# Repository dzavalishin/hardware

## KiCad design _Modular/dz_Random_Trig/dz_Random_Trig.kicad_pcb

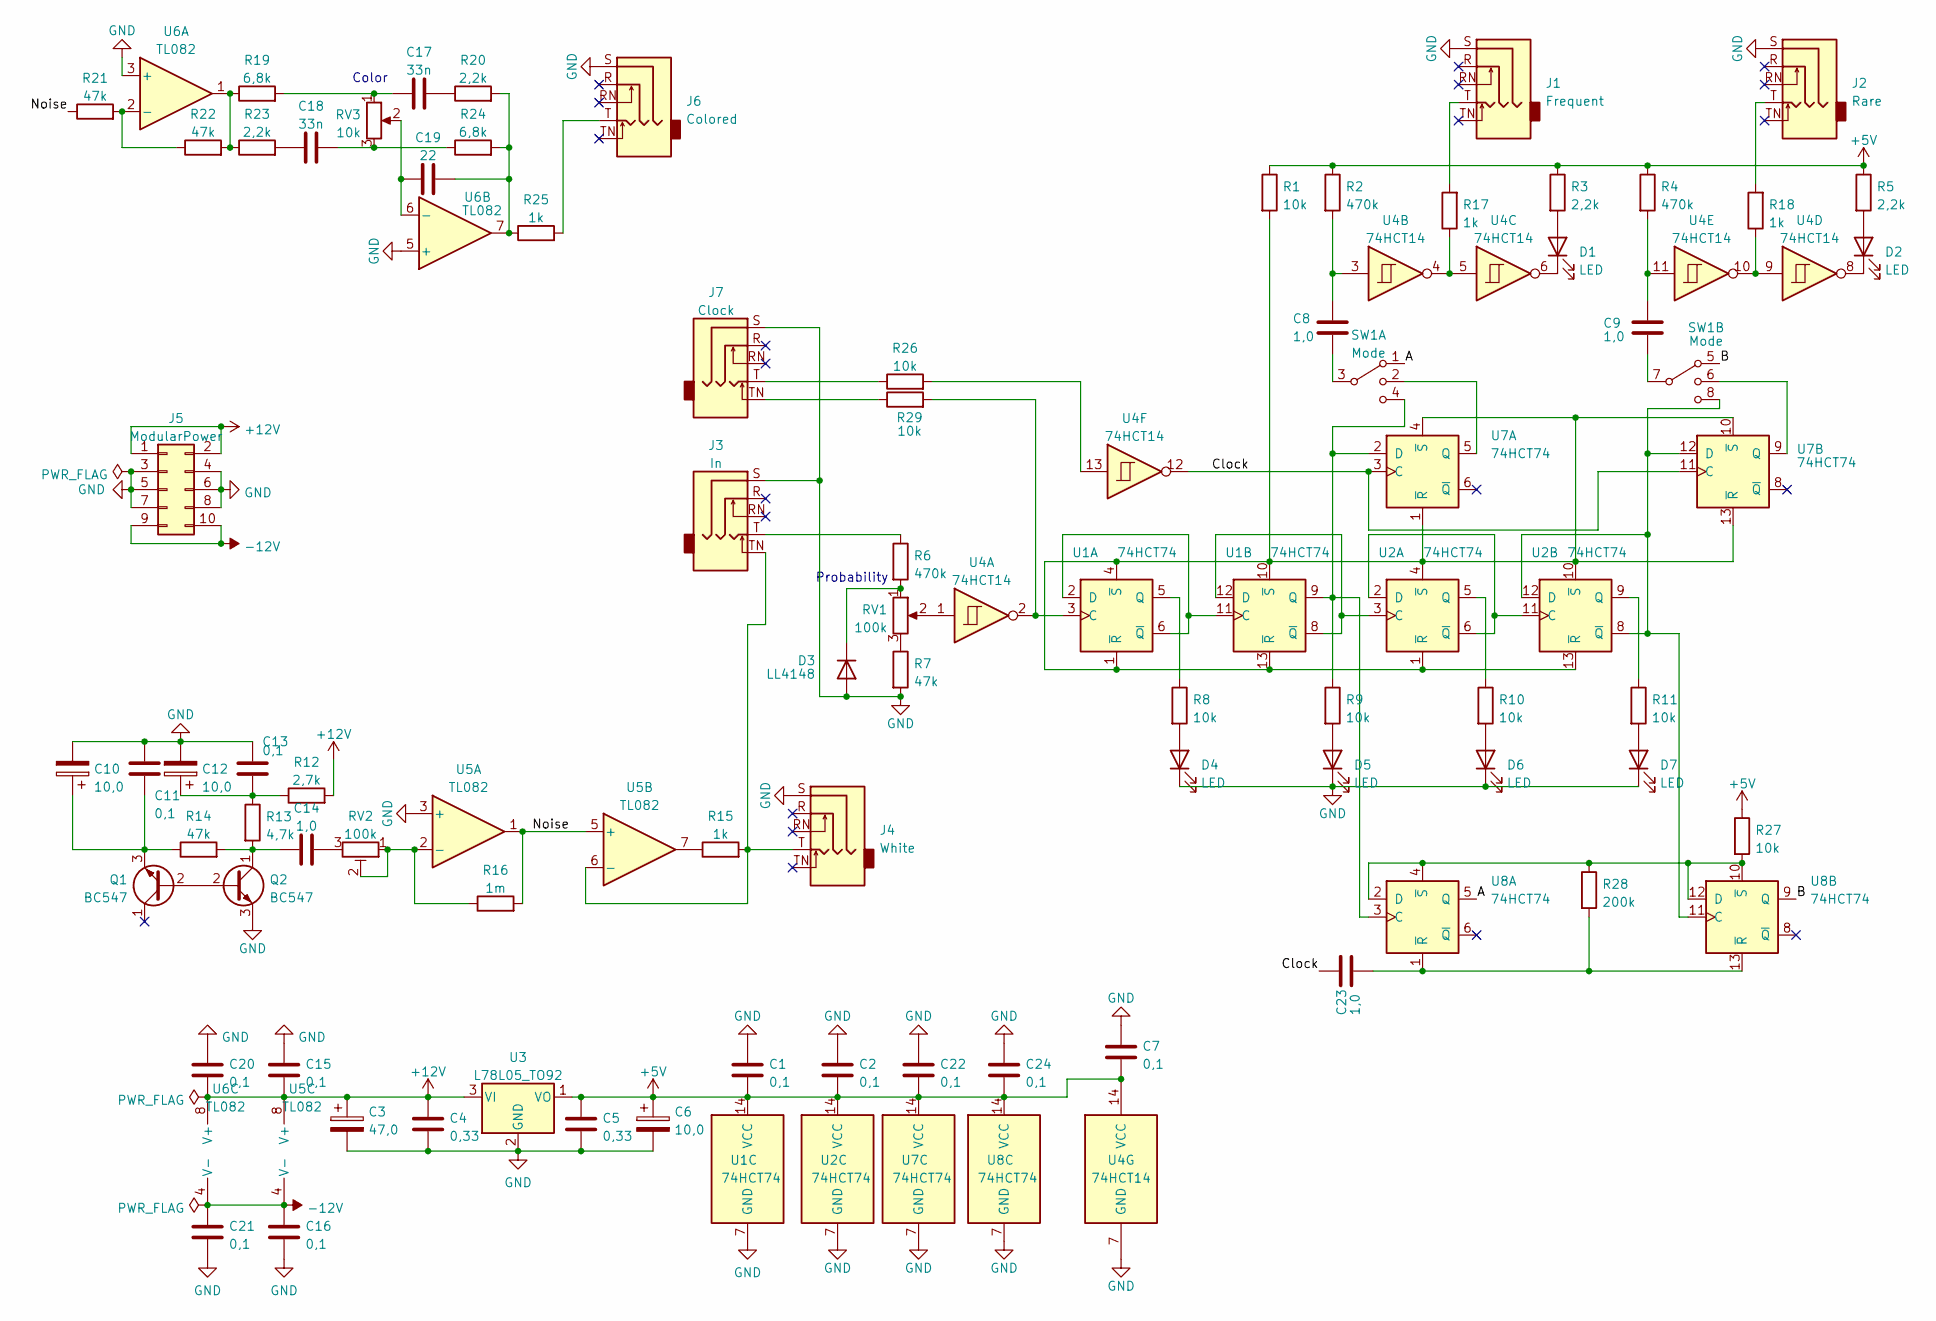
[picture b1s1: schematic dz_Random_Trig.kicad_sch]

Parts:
C1, C2, C7, C11, C13, C15, C16, C20, C21, C22, C24: 0,1; C_0805_2012Metric_Pad1.18x1.45mm_HandSolder
C3: 47,0; CP_Elec_6.3x5.2
C4, C5: 0,33; C_0805_2012Metric_Pad1.18x1.45mm_HandSolder
C6, C10, C12: 10,0; CP_Elec_4x5.4
C8, C9, C14, C23: 1,0; C_0805_2012Metric_Pad1.18x1.45mm_HandSolder
C17, C18: 33n; C_0805_2012Metric_Pad1.18x1.45mm_HandSolder
C19: 22; C_0805_2012Metric_Pad1.18x1.45mm_HandSolder
D1, D2, D4, D5, D6, D7: LED; LED_D3.0mm
D3: LL4148; D_MiniMELF
J1: Frequent; Jack_3.5mm_CUI_SJ1-3525N_Horizontal
J2: Rare; Jack_3.5mm_CUI_SJ1-3525N_Horizontal
J3: In; Jack_3.5mm_CUI_SJ1-3525N_Horizontal
J4: White; Jack_3.5mm_CUI_SJ1-3525N_Horizontal
J5: ModularPower; PinHeader_2x05_P2.54mm_Vertical
J6: Colored; Jack_3.5mm_CUI_SJ1-3525N_Horizontal
J7: Clock; Jack_3.5mm_CUI_SJ1-3525N_Horizontal
Q1, Q2: BC547; TO-92_Inline
R1, R8, R9, R10, R11, R26, R27, R29: 10k; R_0805_2012Metric_Pad1.20x1.40mm_HandSolder
R2, R4, R6: 470k; R_0805_2012Metric_Pad1.20x1.40mm_HandSolder
R3, R5, R20, R23: 2,2k; R_0805_2012Metric_Pad1.20x1.40mm_HandSolder
R7, R14, R21, R22: 47k; R_0805_2012Metric_Pad1.20x1.40mm_HandSolder
R12: 2,7k; R_0805_2012Metric_Pad1.20x1.40mm_HandSolder
R13: 4,7k; R_0805_2012Metric_Pad1.20x1.40mm_HandSolder
R15, R17, R18, R25: 1k; R_0805_2012Metric_Pad1.20x1.40mm_HandSolder
R16: 1m; R_0805_2012Metric_Pad1.20x1.40mm_HandSolder
R19, R24: 6,8k; R_0805_2012Metric_Pad1.20x1.40mm_HandSolder
R28: 200k; R_0805_2012Metric_Pad1.20x1.40mm_HandSolder
RV1: 100k; Potentiometer_Alps_RK097_Single_Horizontal
RV2: 100k; Potentiometer_Runtron_RM-065_Vertical
RV3: 10k; Potentiometer_Alps_RK097_Single_Horizontal
SW1: Mode
U1, U2, U7, U8: 74HCT74; DIP-14_W7.62mm_Socket_LongPads
U3: L78L05_TO92; TO-92_Inline
U4: 74HCT14; DIP-14_W7.62mm_Socket_LongPads
U5, U6: TL082; DIP-8_W7.62mm_Socket_LongPads

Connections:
+5V: C1.2, C2.2, C5.1, C6.1, C7.2, C22.2, C24.2, R1.1, R2.1, R3.1, R4.1, R5.1, R27.1, U1.14 (VCC), U2.14 (VCC), U3.1 (VO), U4.14 (VCC), U7.14 (VCC), U8.14 (VCC)
+12V: C3.1, C4.1, C15.2, C20.2, J5.1, J5.2, R12.2, U3.3 (VI), U5.8 (V+), U6.8 (V+)
-12V: C16.1, C21.1, J5.9, J5.10, U5.4 (V-), U6.4 (V-)
GND: C1.1, C2.1, C3.2, C4.2, C5.2, C6.2, C7.1, C10.2, C11.1, C12.2, C13.1, C15.1, C16.2, C20.1, C21.2, C22.1, C24.1, D3.2 (A), D4.1 (K), D5.1 (K), D6.1 (K), D7.1 (K), J1.S, J2.S, J3.S, J4.S, J5.3, J5.4, J5.5, J5.6, J5.7, J5.8, J6.S, J7.S, Q2.3 (E), R7.2, U1.7 (GND), U2.7 (GND), U3.2 (GND), U4.7 (GND), U5.3 (+), U6.3 (+), U6.5 (+), U7.7 (GND), U8.7 (GND)
unnamed: C8.2, SW1.2, SW1.3, U7.5 (Q)
unnamed: C9.2, SW1.6, SW1.7, U7.9 (Q)
unnamed: C10.1, C11.2, Q1.3 (E), R14.1
unnamed: C12.1, C13.2, R12.1, R13.1
unnamed: C14.1, Q2.1 (C), R13.2, R14.2
unnamed: C14.2, RV2.3
unnamed: C17.1, R19.2, RV3.1
unnamed: C17.2, R20.1
unnamed: C18.1, R23.2
unnamed: C18.2, R24.1, RV3.3
unnamed: C19.1, RV3.2, U6.6 (-)
unnamed: C19.2, R20.2, R24.2, R25.1, U6.7
unnamed: C23.2, R28.2, U8.1 (~R), U8.13 (~R)
unnamed: D1.1 (K), U4.6
unnamed: D1.2 (A), R3.2
unnamed: D2.1 (K), U4.8
unnamed: D2.2 (A), R5.2
unnamed: D3.1 (K), R6.2, RV1.1
unnamed: D4.2 (A), R8.2
unnamed: D5.2 (A), R9.2
unnamed: D6.2 (A), R10.2
unnamed: D7.2 (A), R11.2
unnamed: J1.T, R17.2
unnamed: J2.T, R18.2
unnamed: J3.T, R6.1
unnamed: J6.T, R25.2
unnamed: J7.T, R26.1
unnamed: Q1.2 (B), Q2.2 (B)
unnamed: R7.1, RV1.3
unnamed: R15.1, U5.7
unnamed: R16.1, RV2.1, RV2.2, U5.2 (-)
unnamed: R19.1, R22.2, R23.1, U6.1
unnamed: R21.2, R22.1, U6.2 (-)
unnamed: R26.2, U4.13
unnamed: R27.2, R28.1, U8.2 (D), U8.4 (~S), U8.10 (~S), U8.12 (D)
unnamed: SW1.1, U8.5 (Q)
unnamed: SW1.5, U8.9 (Q)
unnamed: U1.2 (D), U1.6 (~Q), U1.11 (C)
unnamed: R8.1, U1.5 (Q)
unnamed: U1.8 (~Q), U1.12 (D), U2.3 (C)
unnamed: R9.1, SW1.4, U1.9 (Q), U7.2 (D), U8.3 (C)
unnamed: R1.2, U1.1 (~R), U1.4 (~S), U1.10 (~S), U1.13 (~R), U2.1 (~R), U2.4 (~S), U2.10 (~S), U2.13 (~R), U7.1 (~R), U7.4 (~S), U7.10 (~S), U7.13 (~R)
unnamed: R10.1, U2.5 (Q)
unnamed: U2.2 (D), U2.6 (~Q), U2.11 (C)
unnamed: R11.1, U2.9 (Q)
unnamed: SW1.8, U2.8 (~Q), U2.12 (D), U7.12 (D), U8.11 (C)
unnamed: RV1.2, U4.1
unnamed: C8.1, R2.2, U4.3
unnamed: R17.1, U4.4, U4.5
unnamed: R18.1, U4.9, U4.10
unnamed: C9.1, R4.2, U4.11
unnamed: C23.1, U4.12, U7.3 (C), U7.11 (C)

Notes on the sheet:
Probability
Color

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
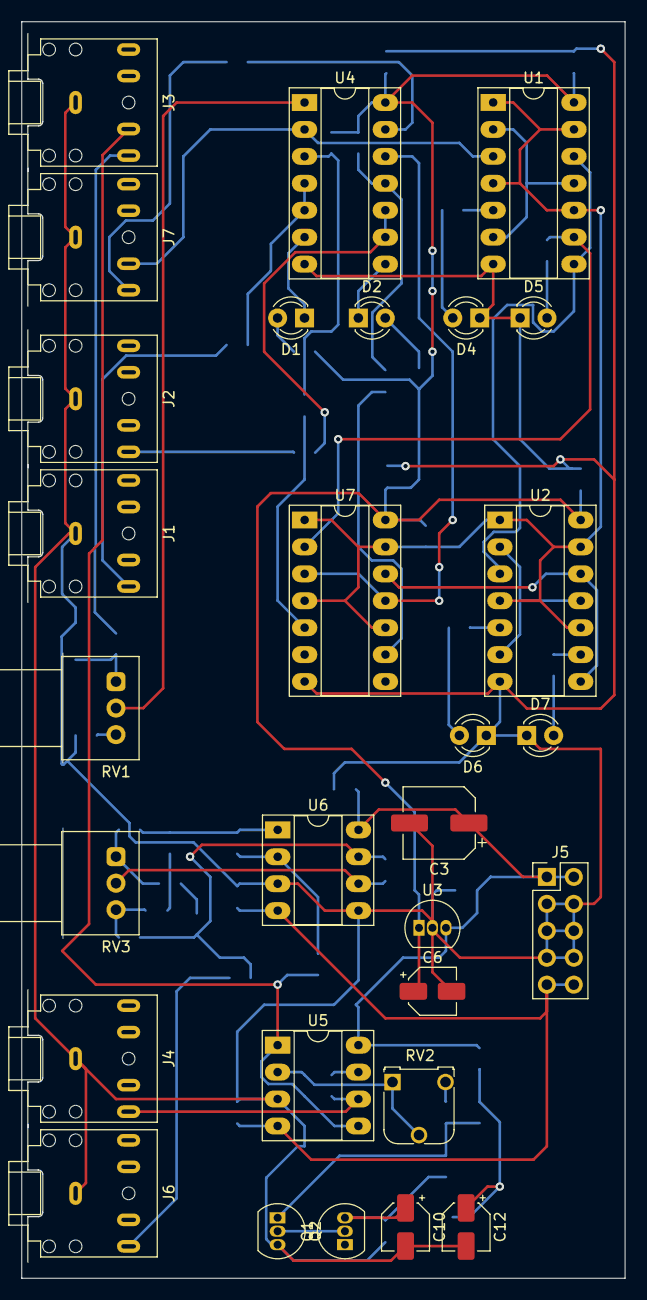
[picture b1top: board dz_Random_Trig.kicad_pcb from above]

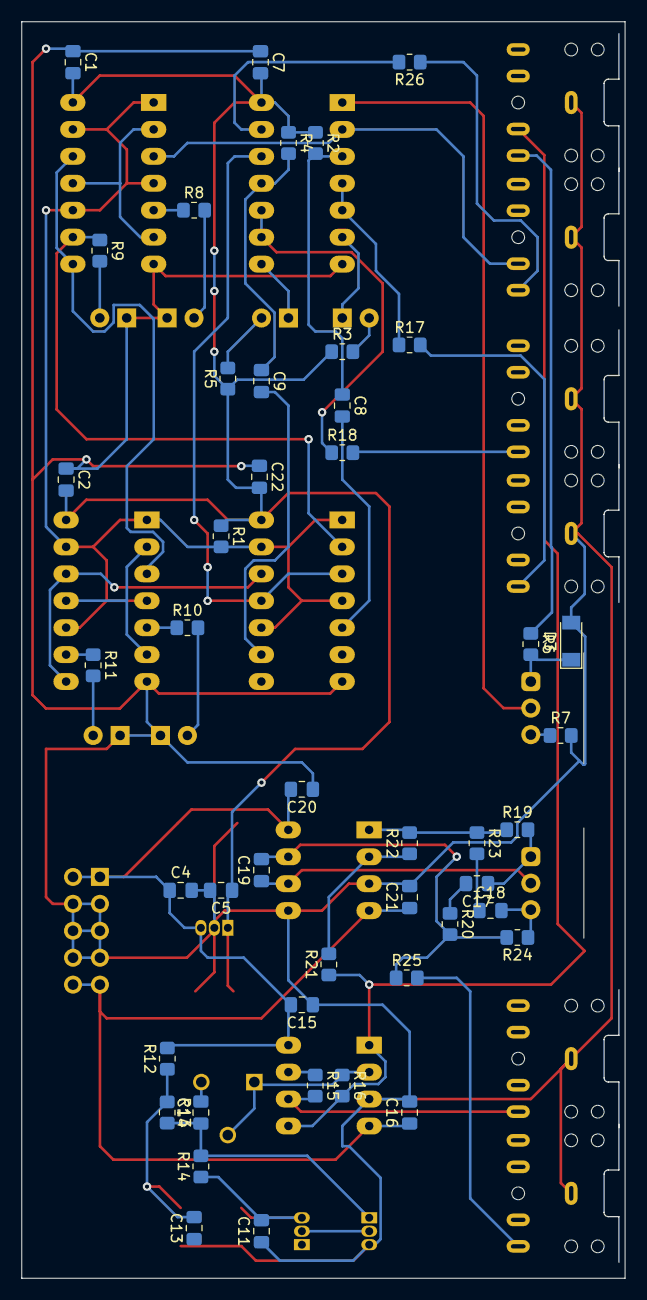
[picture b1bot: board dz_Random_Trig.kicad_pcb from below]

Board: 2 copper layers, 56.9 x 118.5 mm, 74 parts (45 on the bottom side), 55 nets.

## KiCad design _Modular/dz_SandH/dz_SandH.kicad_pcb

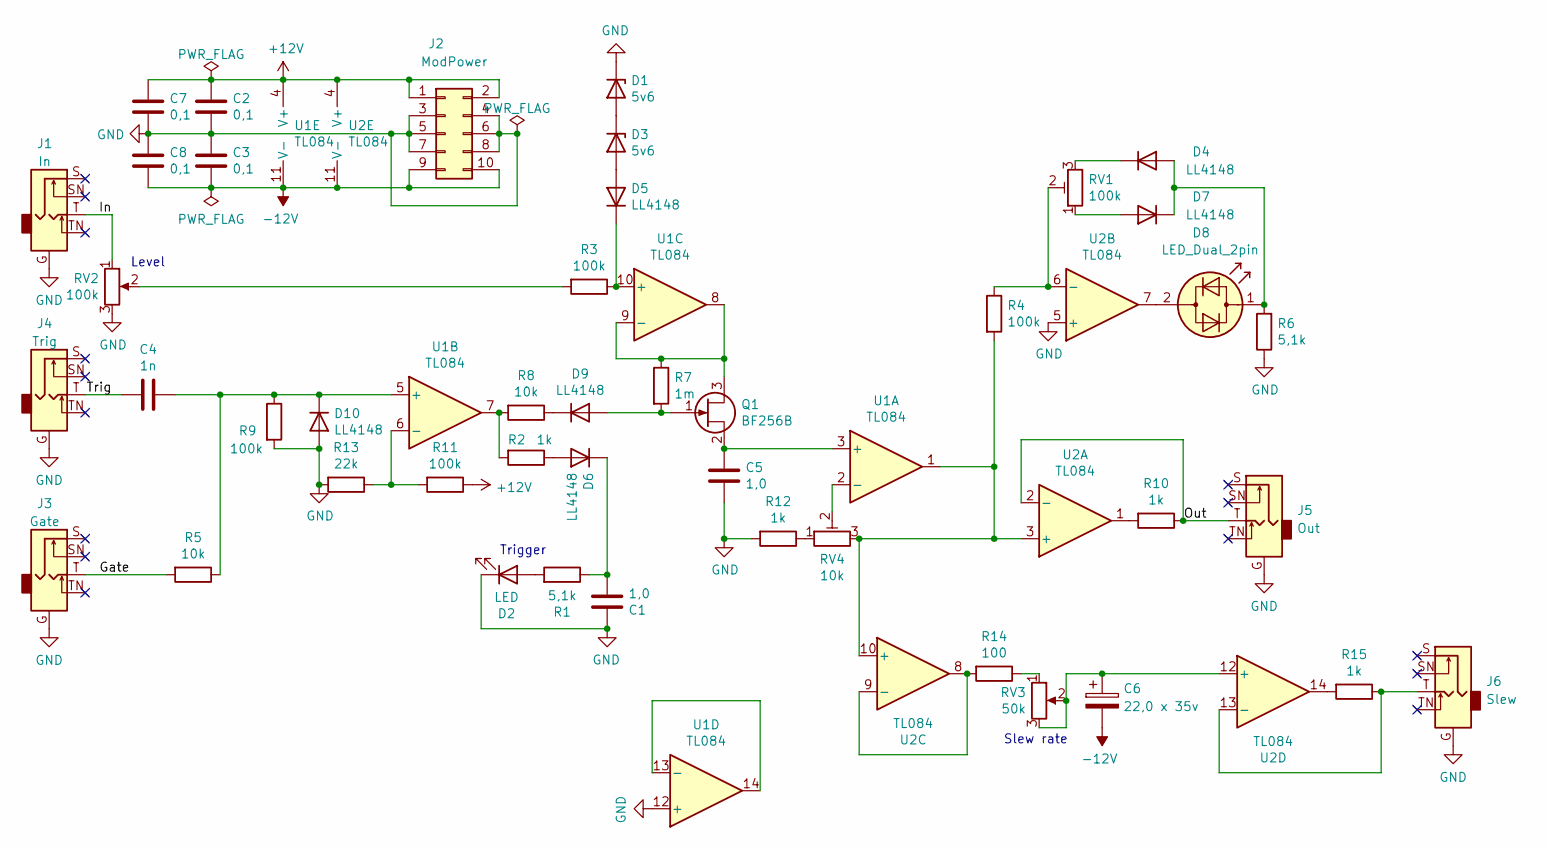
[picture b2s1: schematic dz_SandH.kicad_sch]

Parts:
C1, C5: 1,0; C_0805_2012Metric_Pad1.18x1.45mm_HandSolder
C2, C3, C7, C8: 0,1; C_0805_2012Metric_Pad1.18x1.45mm_HandSolder
C4: 1n; C_0805_2012Metric_Pad1.18x1.45mm_HandSolder
C6: 22,0 x 35v; CP_Radial_D8.0mm_P2.50mm
D1, D3: 5v6; D_MiniMELF_Handsoldering
D2: LED; LED_D3.0mm_Horizontal_O1.27mm_Z2.0mm
D4, D5, D6, D7, D9, D10: LL4148; D_MiniMELF
D8: LED_Dual_2pin; LED_D3.0mm_Horizontal_O1.27mm_Z2.0mm
J1: In; Jack_3.5mm_CUI_SJ1-3525N_Horizontal
J2: ModPower; PinHeader_2x05_P2.54mm_Vertical
J3: Gate; Jack_3.5mm_CUI_SJ1-3525N_Horizontal
J4: Trig; Jack_3.5mm_CUI_SJ1-3525N_Horizontal
J5: Out; Jack_3.5mm_CUI_SJ1-3525N_Horizontal
J6: Slew; Jack_3.5mm_CUI_SJ1-3525N_Horizontal
Q1: BF256B; TO-92
R1, R6: 5,1k; R_0805_2012Metric_Pad1.20x1.40mm_HandSolder
R2, R10, R12, R15: 1k; R_0805_2012Metric_Pad1.20x1.40mm_HandSolder
R3, R4, R9, R11: 100k; R_0805_2012Metric_Pad1.20x1.40mm_HandSolder
R5, R8: 10k; R_0805_2012Metric_Pad1.20x1.40mm_HandSolder
R7: 1m; R_0805_2012Metric_Pad1.20x1.40mm_HandSolder
R13: 22k; R_0805_2012Metric_Pad1.20x1.40mm_HandSolder
R14: 100; R_0805_2012Metric_Pad1.20x1.40mm_HandSolder
RV1: 100k; Potentiometer_Runtron_RM-065_Vertical
RV2: 100k; Potentiometer_Alps_RK097_Single_Horizontal
RV3: 50k; Potentiometer_Alps_RK097_Single_Horizontal
RV4: 10k; Potentiometer_Runtron_RM-065_Vertical
U1, U2: TL084; DIP-14_W7.62mm_Socket_LongPads

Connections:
+12V: C2.1, C7.1, J2.1, J2.2, R11.1, U1.4 (V+), U2.4 (V+)
-12V: C3.2, C6.2, C8.2, J2.9, J2.10, U1.11 (V-), U2.11 (V-)
/Gate: J3.T, R5.2
/In: J1.T, RV2.1
/Out: J5.T, R10.1, U2.2 (-)
/Trig: C4.2, J4.T
GND: C1.1, C2.2, C3.1, C5.2, C7.2, C8.1, D1.1 (K), D2.1 (K), D10.2 (A), J1.G, J2.3, J2.4, J2.5, J2.6, J2.7, J2.8, J3.G, J4.G, J5.G, J6.G, R6.1, R9.2, R12.2, R13.2, RV2.3, U1.12 (+), U2.5 (+)
unnamed: C1.2, D6.1 (K), R1.1
unnamed: C5.1, Q1.2 (S), U1.3 (+)
unnamed: C6.1, RV3.2, RV3.3, U2.12 (+)
unnamed: D1.2 (A), D3.1 (K)
unnamed: D3.2 (A), D5.2 (A)
unnamed: D4.1 (K), RV1.3
unnamed: D4.2 (A), D7.1 (K), D8.1 (KA), R6.2
unnamed: D5.1 (K), R3.1, U1.10 (+)
unnamed: D6.2 (A), R2.1
unnamed: D7.2 (A), RV1.1
unnamed: D8.2 (AK), U2.7
unnamed: C4.1, D10.1 (K), R5.1, R9.1, U1.5 (+)
unnamed: J6.T, R15.1, U2.13 (-)
unnamed: D9.2 (A), Q1.1 (G), R7.2
unnamed: Q1.3 (D), R7.1, U1.8, U1.9 (-)
unnamed: D2.2 (A), R1.2
unnamed: R4.2, RV4.3, U1.1, U2.3 (+), U2.10 (+)
unnamed: D9.1 (K), R8.1
unnamed: R2.2, R8.2, U1.7
unnamed: R10.2, U2.1
unnamed: R11.2, R13.1, U1.6 (-)
unnamed: R12.1, RV4.1
unnamed: R14.1, RV3.1
unnamed: R14.2, U2.8, U2.9 (-)
unnamed: R15.2, U2.14
unnamed: R4.1, RV1.2, U2.6 (-)
unnamed: R3.2, RV2.2
unnamed: RV4.2, U1.2 (-)
unnamed: U1.13 (-), U1.14

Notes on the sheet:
Trigger
Slew rate
Level

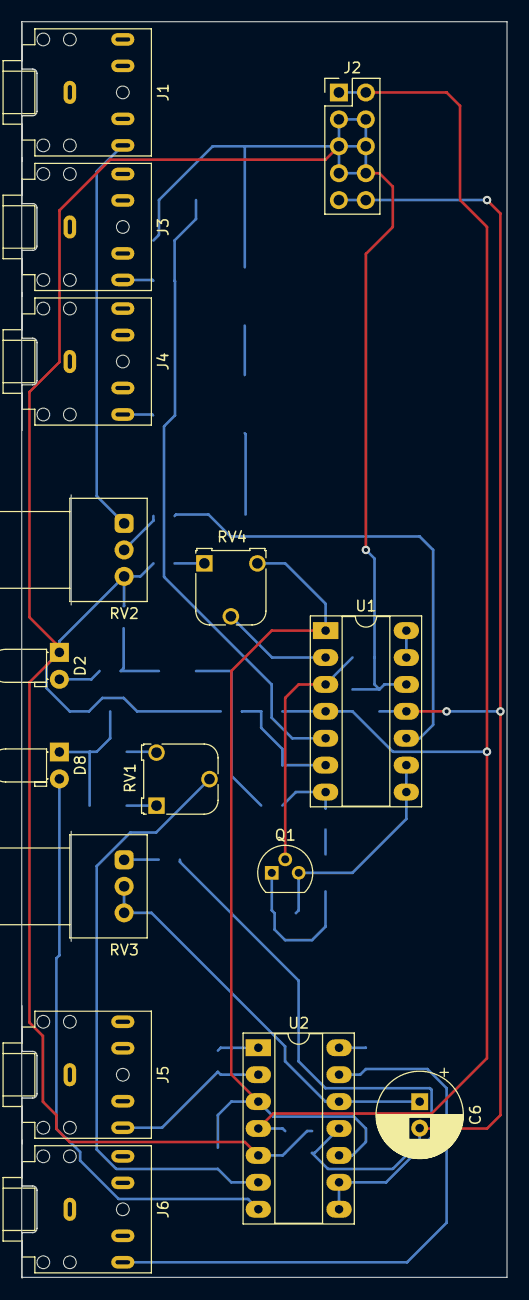
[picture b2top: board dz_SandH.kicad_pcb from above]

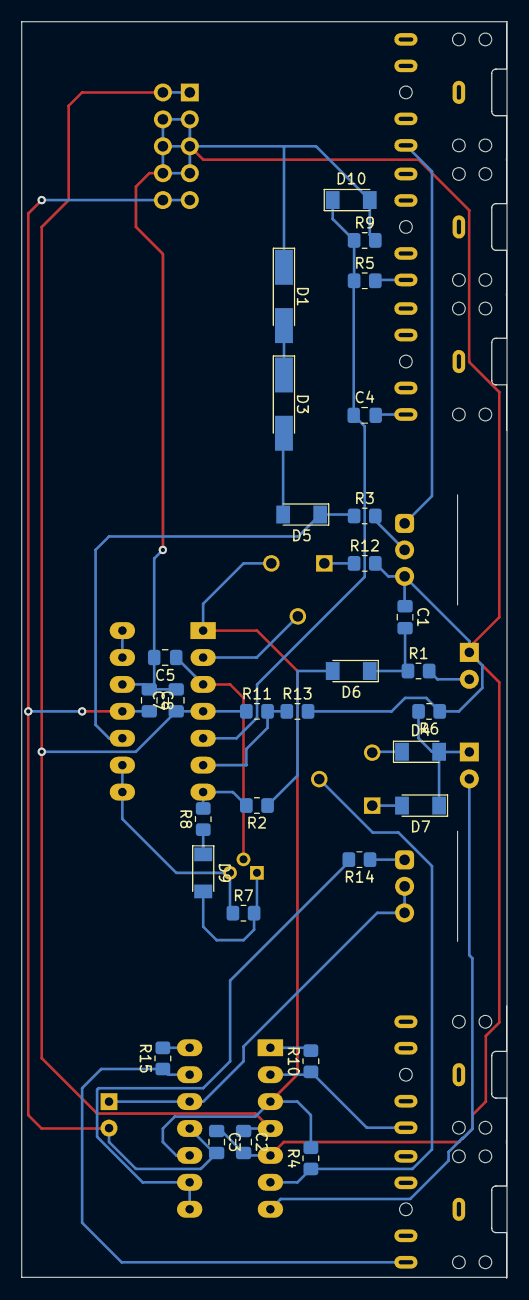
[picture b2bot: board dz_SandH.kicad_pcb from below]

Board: 2 copper layers, 45.8 x 118.5 mm, 46 parts (30 on the bottom side), 36 nets.

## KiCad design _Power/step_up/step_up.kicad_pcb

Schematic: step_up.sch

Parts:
C1, C4, C8, C9, C14, C16, C17: 0,1; C_1206_HandSoldering
C2, C5: 1,0; C_1206_HandSoldering
C3, C6: 47,0; SMD-2112_Pol
C7: 1n; C_1206_HandSoldering
C10: 4700; C_1206_HandSoldering
C11, C15: 10,0; CP_Elec_4x5.3
C12, C13: 0,33; C_1206_HandSoldering
D1: SB360; D_3220
J1: Power; TerminalBlock_bornier-3_P5.08mm
L1: 100uH; Choke_Toroid_8x16mm_Vertical
Q1: IRFR024; TO-252-3_TabPin2
R1, R6, R8: 1k; R_1206_HandSoldering
R2, R3, R5, R9, R11: 3,3k; R_1206_HandSoldering
R4: 0,1; R_2512_HandSoldering
R7: 200k; R_1206_HandSoldering
R10: 1,5k; R_1206_HandSoldering
RV1, RV2: 50k; Potentiometer_Trimmer_Bourns_3296W
U1: 74HC04; DIP-14_W7.62mm
U2: LM2903; DIP-8_W7.62mm
U3: L78L33_TO92; TO-92_Inline_Narrow_Oval

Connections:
+2V5: C14.1, C15.1, R5.2, R10.2, R11.1
+3V3: C11.2, C12.1, C16.1, C17.1, R7.1, R10.1, U1.14 (VCC), U2.8, U3.1 (VO)
+6V: C1.1, C2.1, C3.1, C13.1, J1.3, L1.2, U3.3 (VI)
/+12vOut: C4.1, C5.1, C6.1, D1.1, J1.2, RV2.3
GND: C1.2, C2.2, C3.2, C4.2, C5.2, C6.2, C8.1, C9.2, C10.2, C11.1, C12.2, C13.2, C14.2, C15.2, C16.2, C17.2, J1.1, R4.1, R11.2, RV1.1, RV2.1, U1.7 (GND), U2.4, U3.2 (GND)
unnamed: C7.1, U1.4, U1.5
unnamed: C7.2, R2.2, R3.2
unnamed: C8.2, R6.2, U2.6
unnamed: C9.1, R8.2, U2.5
unnamed: C10.1, R9.2, U2.2
unnamed: D1.2, L1.1, Q1.1
unnamed: Q1.2, U1.10, U1.12
unnamed: Q1.3, R4.2, R6.1
unnamed: R1.1, U1.9, U2.1, U2.7
unnamed: R1.2, U1.6
unnamed: R2.1, U1.1
unnamed: R3.1, U1.2, U1.3
unnamed: R5.1, U2.3
unnamed: R7.2, RV1.3
unnamed: R8.1, RV1.2
unnamed: R9.1, RV2.2
unnamed: U1.8, U1.11, U1.13

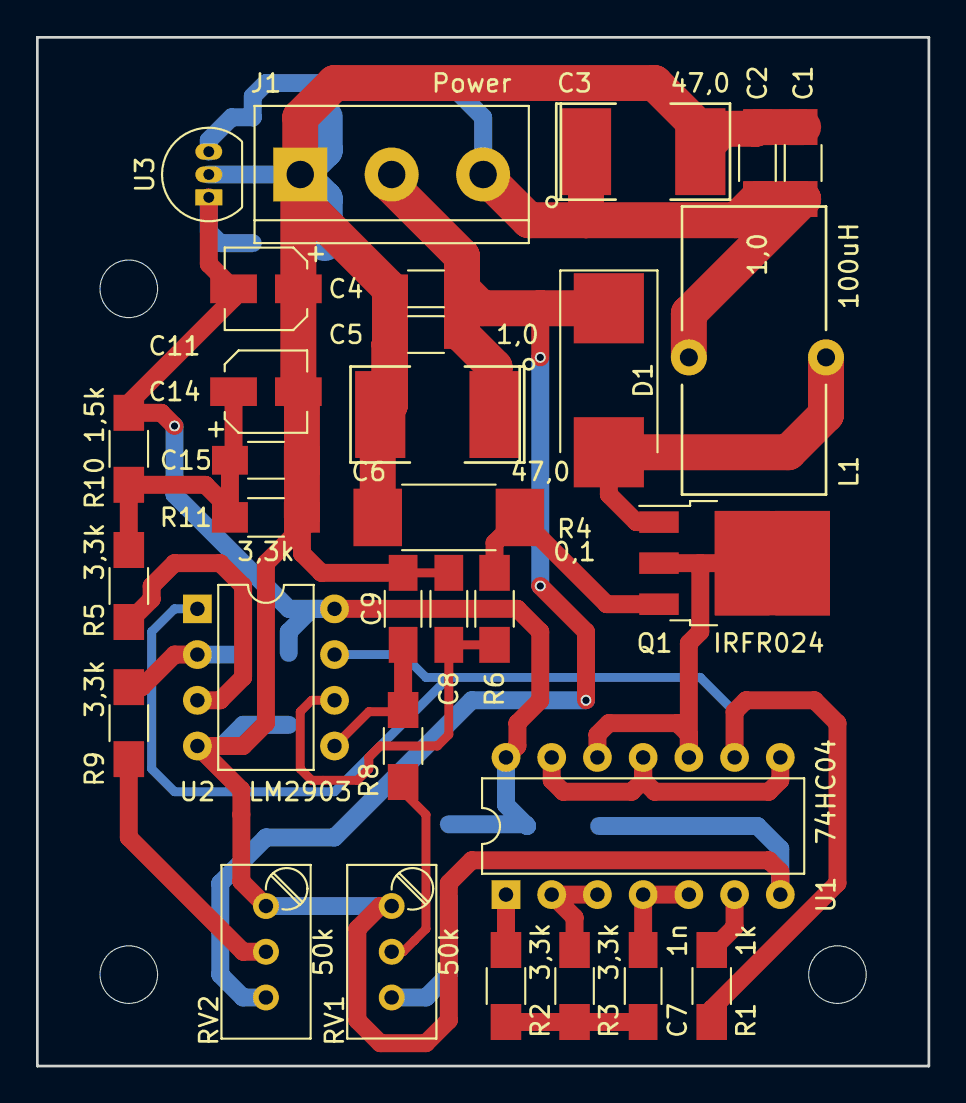
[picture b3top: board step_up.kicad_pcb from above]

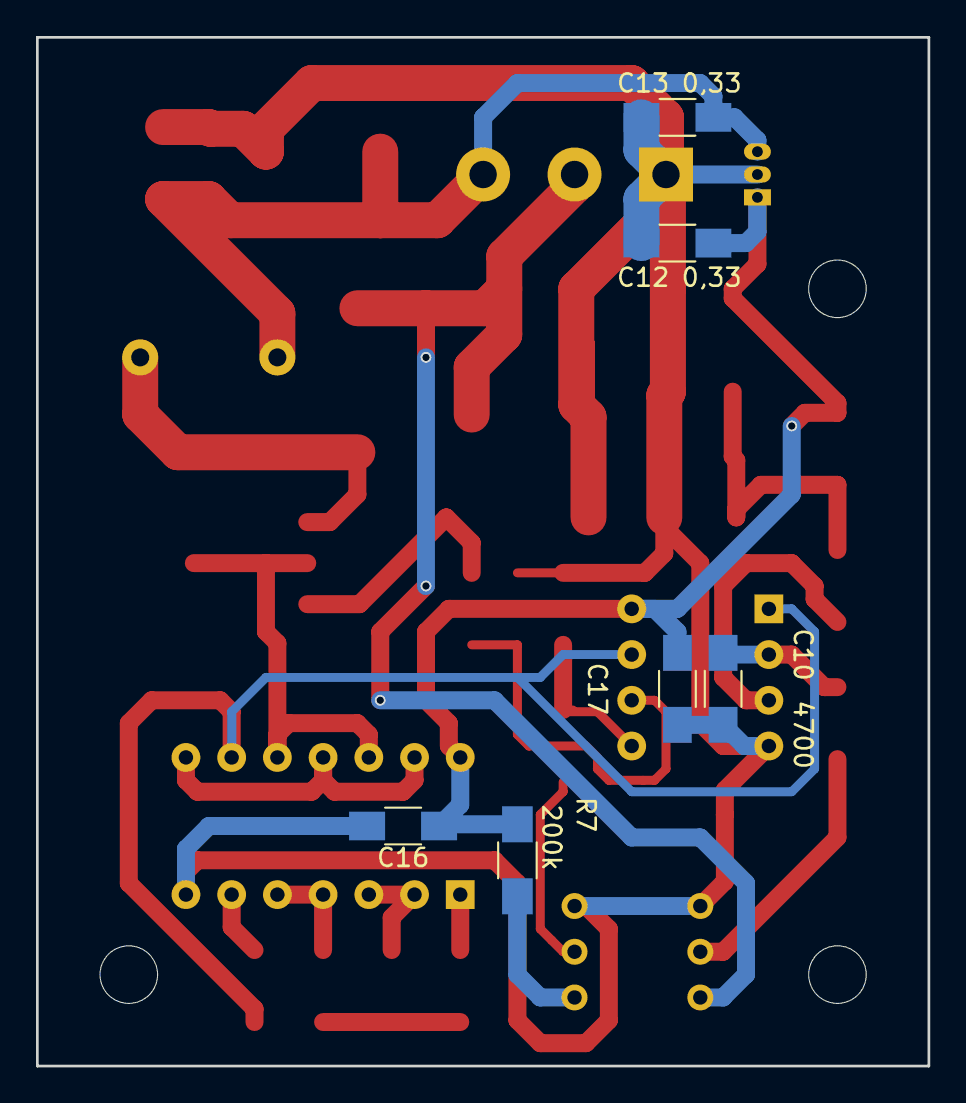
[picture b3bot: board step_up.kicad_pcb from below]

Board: 2 copper layers, 49.5 x 57.1 mm, 37 parts (6 on the bottom side), 22 nets.

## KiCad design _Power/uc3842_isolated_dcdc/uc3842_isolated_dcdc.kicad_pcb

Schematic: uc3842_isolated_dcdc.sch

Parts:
C1, C4, C5, C10, C11, C18: 0,1; C_1206_HandSoldering
C2, C14: 22uF; CP_Elec_6.3x4.5
C3, C6, C9, C12: 470uF; CP_Radial_D6.3mm_P2.50mm
C7: 3n3 100v; C_Disc_D4.3mm_W1.9mm_P5.00mm
C8: 100pF; C_0805_HandSoldering
C13: 470 100v; C_Disc_D4.3mm_W1.9mm_P5.00mm
C15: 10n; C_0805_HandSoldering
C16: 2n2; C_0805_HandSoldering
C17: 470; C_0805_HandSoldering
D1, D3, D4, D6, D7, D8, D9, D10: 1N5822; D_SMA
D2: 5v6; D_MiniMELF_Handsoldering
D5: TL431LP; TO-92_Molded_Narrow
J1: +24; TerminalBlock_bornier-2_P5.08mm
J2: Out; Pin_Header_Straight_1x04_Pitch2.54mm
L1: 100uH; cd54
MH1, MH2, MH3, MH4: MountingHole; MountingHole_3.2mm_M3
Q1: IRFR024N; TO-252-2
R1: 560; R_1206_HandSoldering
R2: 1k5 1W; R_2512_HandSoldering
R3, R9: 22; R_1206_HandSoldering
R4: 470; R_1206_HandSoldering
R5, R6, R7, R10, R13: 3,3k; R_1206_HandSoldering
R8: 150k; R_1206_HandSoldering
R11: 10k; R_1206_HandSoldering
R12: 1k; R_1206_HandSoldering
R14: 20k; R_1206_HandSoldering
R15: 0,55 1W; R_2512_HandSoldering
R16: 750 1W; R_2512_HandSoldering
T1: EE16_24_05_Transformer; EE16_Transformer
U1: LTV-817S; SMDIP-4_W9.53mm
U2: UC3842; DIP-8_W7.62mm_LongPads

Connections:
/+5A: C11.1, C12.1, J2.2, L1.1, R1.2, R6.2, U1.1; also elsewhere on the board
/+5B: C5.1, C6.1, D2.1, J2.4, R3.1; also elsewhere on the board
/+24: C1.1, C2.1, C7.2, C18.1, D1.1 (K), R2.2, T1.1, U1.4, U2.7
/-5A: C9.2, C10.2, C11.2, C12.2, D5.2, J2.1, R10.1, T1.4; also elsewhere on the board
/-5B: C3.2, C4.2, C5.2, C6.2, D2.2, J2.3, T1.7; also elsewhere on the board
GND: C1.2, C2.2, C14.2, C15.1, C16.1, C17.1, C18.2, D7.2 (A), D8.1 (K), J1.1, R13.1, R14.1, R15.1, R16.1, U2.5
unnamed: C3.1, C4.1, D6.1 (K), D10.1 (K), R3.2
unnamed: C7.1, D4.1 (K), R2.1
unnamed: C8.1, R8.1, U2.1
unnamed: C8.2, R7.1, R8.2, R13.2, U2.2
unnamed: C9.1, C10.1, D3.1 (K), D9.1 (K), L1.2
unnamed: C13.1, D8.2 (A), R16.2
unnamed: C13.2, D4.2 (A), Q1.2, T1.10
unnamed: C14.1, R5.1, R7.2
unnamed: C15.2, R11.2, U2.8
unnamed: C16.2, R11.1, U2.4
unnamed: C17.2, R12.2, U2.3
unnamed: D1.2 (A), J1.2
unnamed: D3.2 (A), T1.5
unnamed: D5.1, R6.1, R10.2
unnamed: D5.3, R1.1, R4.1
unnamed: D6.2 (A), T1.6
unnamed: D7.1 (K), R9.2, U2.6
unnamed: D9.2 (A), T1.3
unnamed: D10.2 (A), T1.8
unnamed: Q1.1, R9.1, R14.2
unnamed: Q1.3, R12.1, R15.2
unnamed: R4.2, U1.2
unnamed: R5.2, U1.3

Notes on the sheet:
Used 18 in test

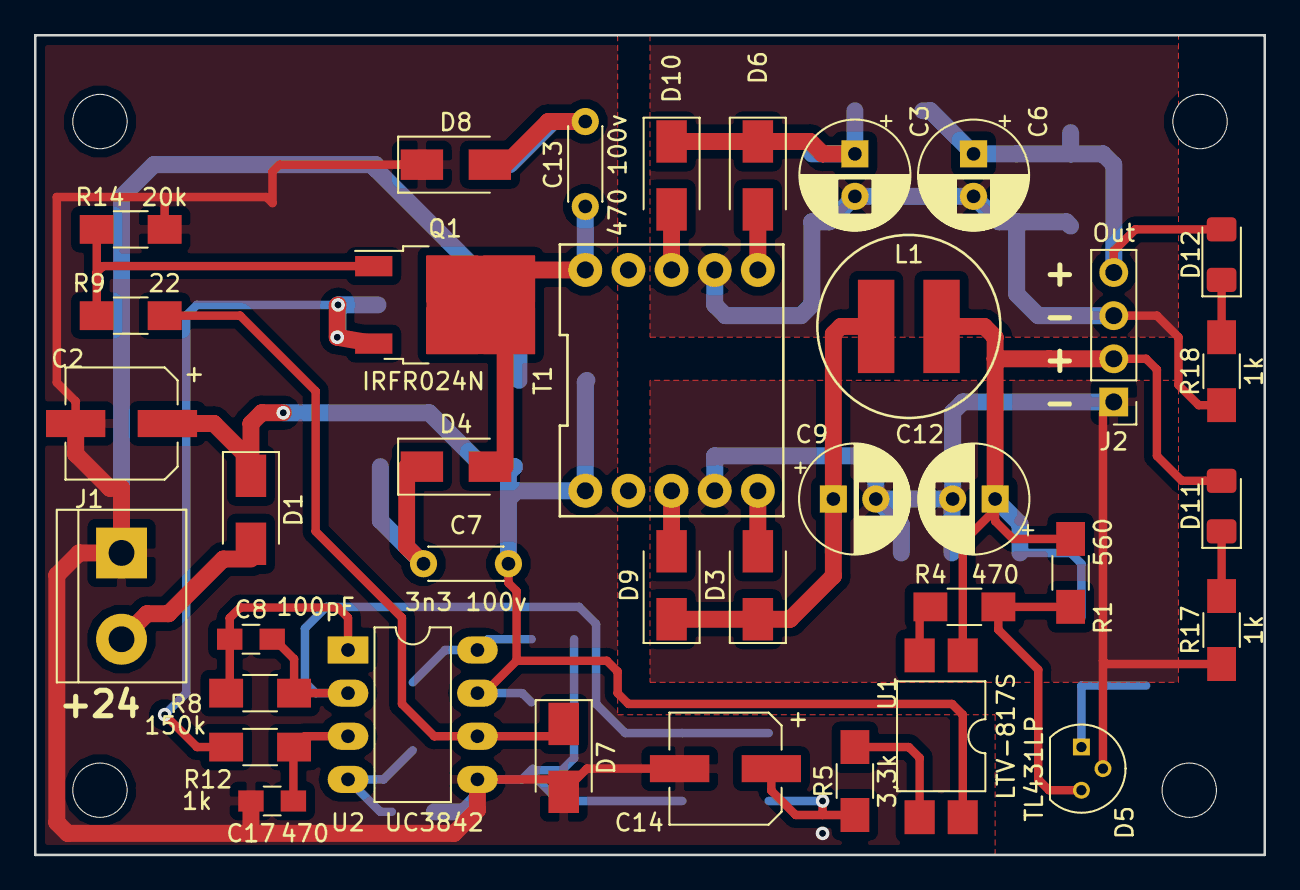
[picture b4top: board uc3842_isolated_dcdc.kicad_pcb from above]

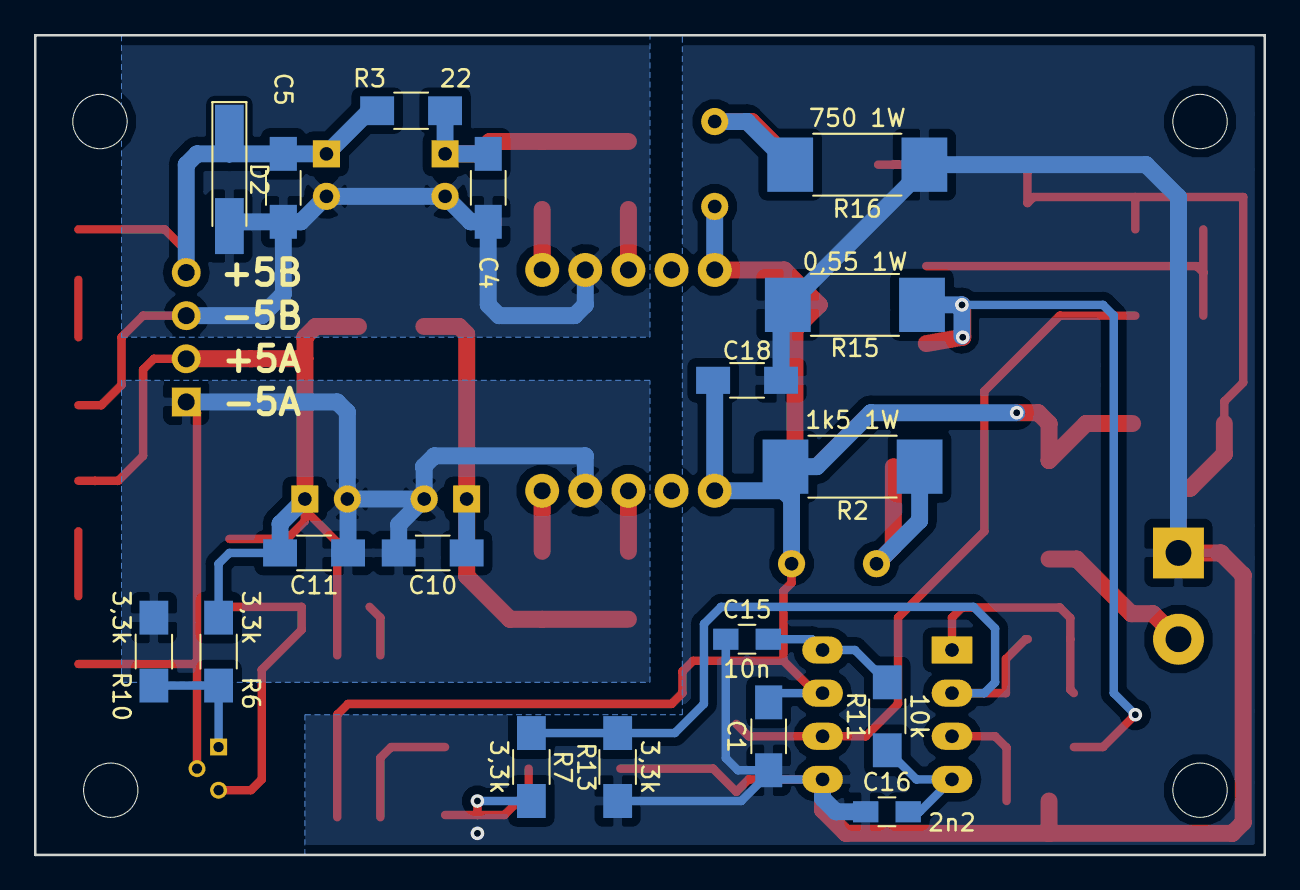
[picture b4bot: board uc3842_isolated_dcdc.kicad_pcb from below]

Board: 2 copper layers, 72.4 x 48.3 mm, 59 parts (18 on the bottom side), 31 nets.

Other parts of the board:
D11, D12: LED; LED_1206_3216Metric_Pad1.42x1.75mm_HandSolder
R17, R18: 1k; R_1206_HandSoldering

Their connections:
/+5A: D11.2; also elsewhere on the board
/+5B: D12.2; also elsewhere on the board
/-5A: R17.1; also elsewhere on the board
/-5B: R18.1; also elsewhere on the board
unnamed: D11.1, R17.2
unnamed: D12.1, R18.2

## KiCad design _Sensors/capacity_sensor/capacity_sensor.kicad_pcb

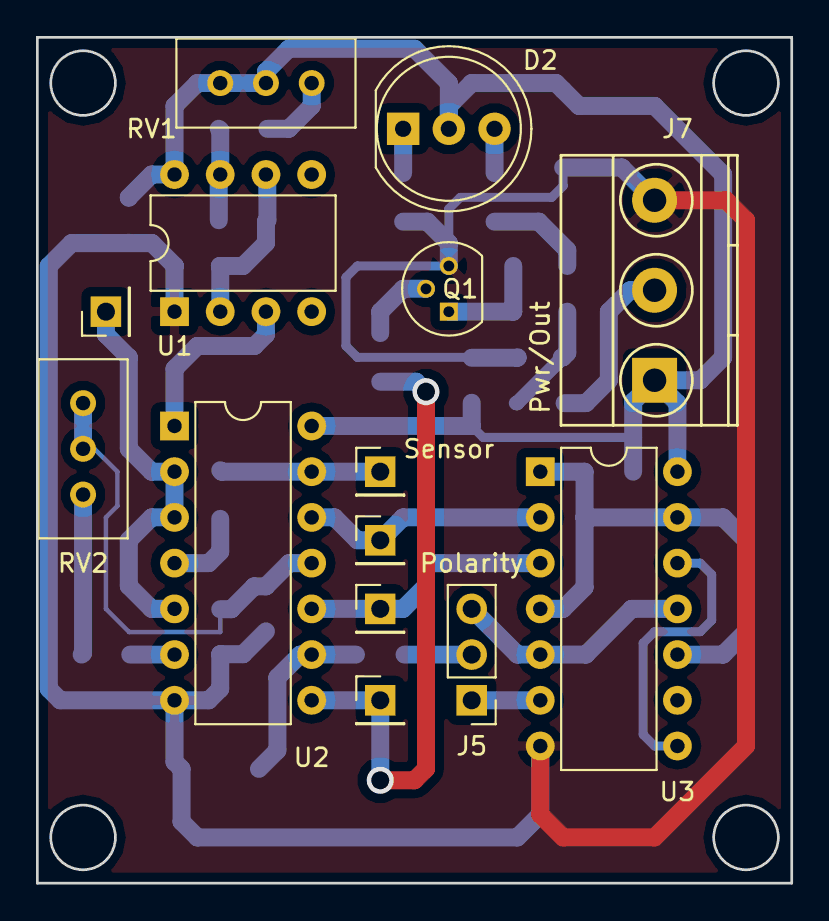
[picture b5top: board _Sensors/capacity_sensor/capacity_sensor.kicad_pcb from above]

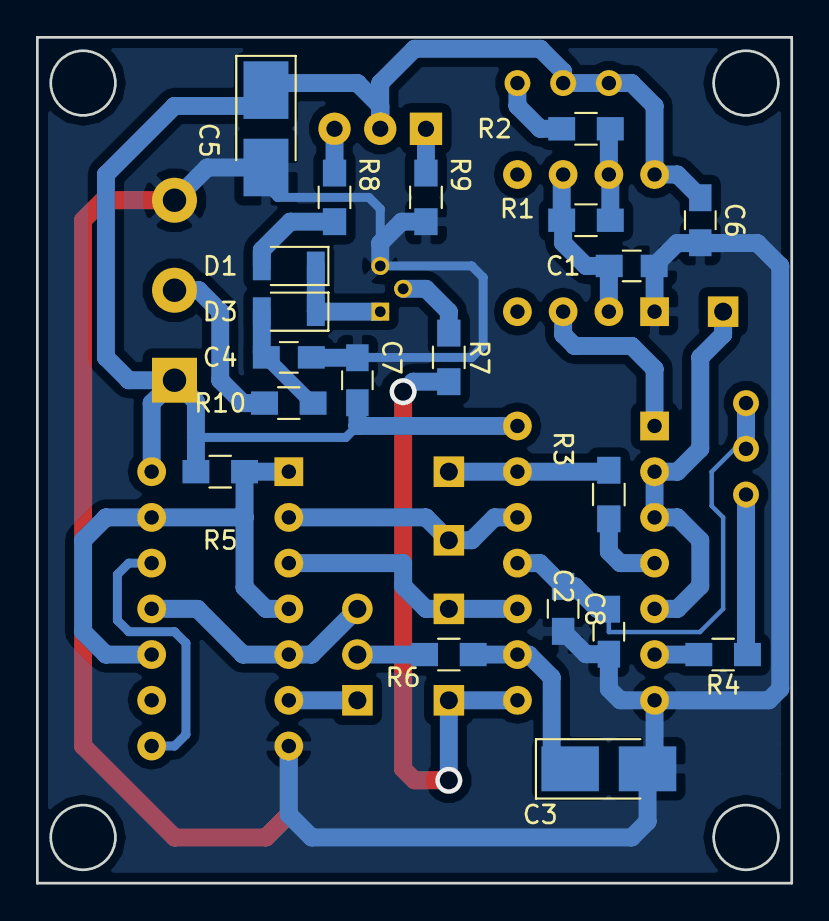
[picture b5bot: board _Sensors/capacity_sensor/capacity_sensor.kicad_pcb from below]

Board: 2 copper layers, 41.9 x 47.0 mm, 34 parts (20 on the bottom side), 28 nets.

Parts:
C1: 2n2; C_0805_HandSoldering
C2: 10pF; C_0805_HandSoldering
C3, C5: 10,0; CP_Tantalum_Case-B_EIA-3528-21_Hand
C4, C6, C7: 0,1; C_0805_HandSoldering
C8: 4,7pF; C_0805_HandSoldering
D1, D3: 1N4148; D_1206
D2: LED_Dual_CAC; LED_D8.0mm-3
J1: TP1; Pin_Header_Straight_1x01_Pitch2.54mm
J2: Sensor; Pin_Header_Straight_1x01_Pitch2.54mm
J3: TP2; Pin_Header_Straight_1x01_Pitch2.54mm
J4: TP3; Pin_Header_Straight_1x01_Pitch2.54mm
J5: Polarity; Pin_Header_Straight_1x03_Pitch2.54mm
J6: TP4; Pin_Header_Straight_1x01_Pitch2.54mm
J7: Pwr/Out; TerminalBlock_Phoenix_MKDS1.5-3pol
Q1: BC546; TO-92_Molded_Narrow
R1, R2, R5, R7, R8: 1k; R_0805_HandSoldering
R3, R6: 10k; R_0805_HandSoldering
R4: 2k; R_0805_HandSoldering
R9: 5k6; R_0805_HandSoldering
R10: 100; R_0805_HandSoldering
RV1: 10k; Potentiometer_Trimmer_Suntan_TSR-3386C_Vertical
RV2: 50k; Potentiometer_Trimmer_Suntan_TSR-3386C_Vertical
U1: ICM7555; DIP-8_W7.62mm
U2: 74HCT14; DIP-14_W7.62mm
U3: 74HC74; DIP-14_W7.62mm

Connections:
+5V: C5.1, C6.1, C7.2, D2.2, J7.1, R5.1, RV1.1, RV1.2, U1.8, U2.14, U3.14
GND: C1.2, C2.2, C3.2, C4.2, C5.2, C6.2, C7.1, C8.2, J7.3, Q1.3, R9.1, U1.1, U2.7, U3.7
unnamed: C1.1, R1.2, U1.2, U1.6
unnamed: C2.1, C8.1, RV2.1, RV2.2, U2.11
unnamed: C3.1, R6.1, U2.9
unnamed: C4.1, D3.2, R10.2
unnamed: D1.1, D3.1, Q1.1
unnamed: D1.2, R8.1
unnamed: D2.1, R9.2
unnamed: D2.3, R8.2
unnamed: J1.1, U2.2, U2.3, U2.5
unnamed: J2.1, R3.1, U2.13
unnamed: J3.1, U2.12, U3.2
unnamed: J4.1, U2.10, U3.3
unnamed: J5.1, U3.6
unnamed: J5.2, R6.2
unnamed: J5.3, U3.5, U3.11
unnamed: J6.1, R7.2, U2.8
unnamed: J7.2, R10.1
unnamed: Q1.2, R7.1
unnamed: R1.1, R2.2, U1.7
unnamed: R2.1, RV1.3
unnamed: R3.2, U2.4
unnamed: R4.1, RV2.3
unnamed: R4.2, U2.6
unnamed: R5.2, U3.1, U3.4, U3.10, U3.13
unnamed: U1.3, U2.1
unnamed: U3.8, U3.12

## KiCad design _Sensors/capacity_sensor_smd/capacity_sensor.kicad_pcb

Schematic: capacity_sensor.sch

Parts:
C1, C7, C8, C9, C10: 0,1; C_0805_HandSoldering
C2: 2n2; C_0805_HandSoldering
C3: 10pF; C_0805_HandSoldering
C4: 4,7pF; C_0805_HandSoldering
C5, C11: 10,0; CP_Tantalum_Case-A_EIA-3216-18_Hand
C6: 10,0; CP_Tantalum_Case-B_EIA-3528-21_Hand
C12, C13: 0,33; C_0805_HandSoldering
D1: Out; LED_1206_HandSoldering
D2, D3: 1N4148; D_1206
D4: Pwr; LED_1206_HandSoldering
D5: 1N4148; D_PowerDI-123
J1: TP1; Pin_Header_Straight_1x01_Pitch2.54mm
J2: Sensor; Pin_Header_Straight_1x01_Pitch2.54mm
J3: TP2; Pin_Header_Straight_1x01_Pitch2.54mm
J4: TP3; Pin_Header_Straight_1x01_Pitch2.54mm
J6: TP4; Pin_Header_Straight_1x01_Pitch2.54mm
J7: Pwr/Out; TerminalBlock_Altech_AK300-3_P5.00mm
JP1: Jumper_NO_Small; SolderJumper-2_P1.3mm_Open_TrianglePad1.0x1.5mm
MH1, MH2, MH3, MH4: MountingHole; MountingHole_3.2mm_M3
Q1: 2N2222; SOT-23_Handsoldering
R1, R2, R5, R7, R8: 1k; R_0805_HandSoldering
R3, R6: 10k; R_0805_HandSoldering
R4: 2k; R_0805_HandSoldering
R9: 5k6; R_0805_HandSoldering
R10: 100; R_0805_HandSoldering
R11: 200; R_2512_HandSoldering
RV2: 50k; Potentiometer_Trimmer_Suntan_TSR-3386C_Vertical
U1: ICM7555; DIP-8_W7.62mm
U2: 74HCT14; SOIC-14_3.9x8.7mm_Pitch1.27mm
U3: 74HC74; SOIC-14_3.9x8.7mm_Pitch1.27mm
U4: L78L05_SOT89; SOT89-3_Housing

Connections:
+5V: C1.1, C5.1, C8.2, C9.2, C10.2, C13.2, D1.2, D4.2, JP1.2, R2.1, R5.1, U1.8 (VCC), U2.14 (VCC), U3.14 (VCC), U4.1 (OUT)
+24V: D5.1, J7.1, R11.2
GND: C1.2, C2.2, C3.2, C4.2, C5.2, C6.2, C7.2, C8.1, C9.1, C10.1, C11.2, C12.1, C13.1, J7.3, Q1.2, R9.1, U1.1 (GND), U2.7 (GND), U3.7 (GND), U4.2 (GND)
unnamed: C2.1, R1.2, U1.2 (TR), U1.6 (THR)
unnamed: C3.1, C4.1, RV2.1, RV2.2, U2.11
unnamed: C6.1, R6.1, U2.13
unnamed: C7.1, D3.2, D5.2, R10.2
unnamed: C11.1, C12.2, JP1.1, R11.1, U4.3 (IN)
unnamed: D1.1, R8.2
unnamed: D2.1, D3.1, Q1.3
unnamed: D2.2, R8.1
unnamed: D4.1, R9.2
unnamed: J1.1, U2.2, U2.3, U2.5
unnamed: J2.1, R3.1, U2.9
unnamed: J3.1, U2.8, U3.3 (Cp)
unnamed: J4.1, U2.10, U3.2 (D)
unnamed: J6.1, R7.2, U2.12
unnamed: J7.2, R10.1
unnamed: Q1.1, R7.1
unnamed: R1.1, R2.2, U1.7 (DIS)
unnamed: R3.2, U2.4
unnamed: R4.1, RV2.3
unnamed: R4.2, U2.6
unnamed: R5.2, U3.1 (Cd), U3.4 (Sd), U3.10 (Sd), U3.11 (Cp), U3.12 (D), U3.13 (Cd)
unnamed: R6.2, U3.6 (~Q)
unnamed: U1.3 (Q), U2.1
